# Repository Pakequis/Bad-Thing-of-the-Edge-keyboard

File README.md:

# **Bad Thing of the Edge keyboard**
A mechanical gamer keyboard for left hand with Raspberry Pi Pico.

## Why another mechanical keyboard?

Sometimes I play **Diablo 3** on my small 7-inch laptop and have difficulty with the keyboard. The keys are very small and the placement is a little different from a regular keyboard. Yes, I could remap the keys or use a regular keyboard, but it wouldn't be as fun as making my own keyboard.

The keyboard layout was made for my left hand with the main four fingers on the skills buttons and the thumb on the potion button.

~~It should work for Diablo 4 (the action keys are mostly in the same positions), but I haven't tested it yet (**$$$**). For other games, you need to change the buttons table in the firmware.~~

[Update 05/19/2024] I remapped the keys to work in both Diablo 3 and Diablo 4.

## Demo video:

## Hardware:

The boards were developed in kicad 7.0. There are two PCBs, one for the keyboard (Main-board) and another for the panel. The two boards are stacked and secured with M3 screws and 8 mm spacers.

External libraries used in the project:

[Key Switchs library for Kicad by Rafael Silva.](https://github.com/kiswitch/kiswitch)

[Raspberry Pi Pico by Nicolò Carandini.](https://github.com/ncarandini/KiCad-RP-Pico)

I used two-piece clear keycaps for the keys ([bought on Aliexpress](https://s.click.aliexpress.com/e/_DEuJarX) - **Affiliate link!**). I printed the button images, cut them out and put them inside the keycaps.

Bars for the LEDs were made into the panel board with keep out areas on the top and bottom copper layers and the bottom solder mask layer. When the LEDs on the main board turn on, the light is scattered on these bars. I used red LEDs to contrast with the black solder mask and match the horror theme of the keyboard.

The stack:

Mechanical keys are Cherry MX type, but in the prototype I took the keys from a old PTZ camera controller.

Files here are from the second version of the boards, with corrections made to the prototype. The photos and videos are from the prototype. One problem I had with the prototype panel board was that I didn't put the keep out area on the bottom solder mask layer. So I had to sand these areas and the effect was even better than I expected. Here the affected area:

Second board revision sponsored by [PCBWay](https://www.pcbway.com).

## Firmware:

The firmware was made in [VSCode](https://code.visualstudio.com/) with the [PlatformIO](https://platformio.org/) extension and the [Arduino-Pico core](https://github.com/earlephilhower/arduino-pico), using [Adafruit's TinyUSB library](https://github.com/adafruit/Adafruit_TinyUSB_Arduino). Core 0 is responsible for the keyboard and Core 1 for the LED effects. It was a bit over the top, but I wanted to test this functionality.

The keyboard part was made using the [example from Adafruit's TinyUSB library](https://github.com/adafruit/Adafruit_TinyUSB_Arduino/blob/master/examples/HID/hid_boot_keyboard/hid_boot_keyboard.ino).

The LED effects in this first version are:
- **Breath** - Up and down the bright of the LED bars.
- **Noise** - Random change in the bright of the bars.
- **Breath 2** - Same as the first one, but the center bar changes the brightness first.
- **Keypress** - Flashes the bars when a key is pressed.
- **Quake Flicker** - The classical [fluorescent Quake's flashing lights](https://github.com/Pakequis/arduino-quake-flicker-lamp).

One of the keys - the first one on the top - was exclusive to change the effect of the LEDs. When it is pressed, the bars flash indicating the change and the new effect starts working. Effects are saved in one byte of the FLASH memory and retrieved on power on.

## Bad Thing of What?
The name comes from a famous Brazilian case of haunted house and exorcism that happened in 1953. On one of the exorcism nights, Father Pedro Cintra asked in Latin: **"Praecipio ibi ut dicas qui sis tu"** ("I command you to tell me who you are"). A monstrous voice then replied in Portuguese: **"Eu sou o Diabo!"** ("I am the Devil!").

But people didn't pronounce that name and called the entity just **"Coisa Ruim"** ("Bad Thing", but "Evil Thing" would be better ) when the rumors spread. They added part of the name of the city where the case took place, **Borda da Mata** (something like "Edge of the Woods"), and started to call it Coisa Ruim da Borda (Bad Thing of the Edge).

I found an [article in a magazine of the time with a picture of the haunted house](http://memoria.bn.br/DocReader/DocReader.aspx?bib=003581&pagfis=86382) (in Portuguese - page 102).

## Known issues:
- The position of the Raspberry pi pico on the board is not good and some USB cables may not fit between the boards.
- It lacks a case for 3D printing. 
- The positioning of the LEDs could be improved.

## Contact:

Feel free to reach out to me on social media: @pakequis in any of them...

You can also send me an email at pakequis (Gmail).

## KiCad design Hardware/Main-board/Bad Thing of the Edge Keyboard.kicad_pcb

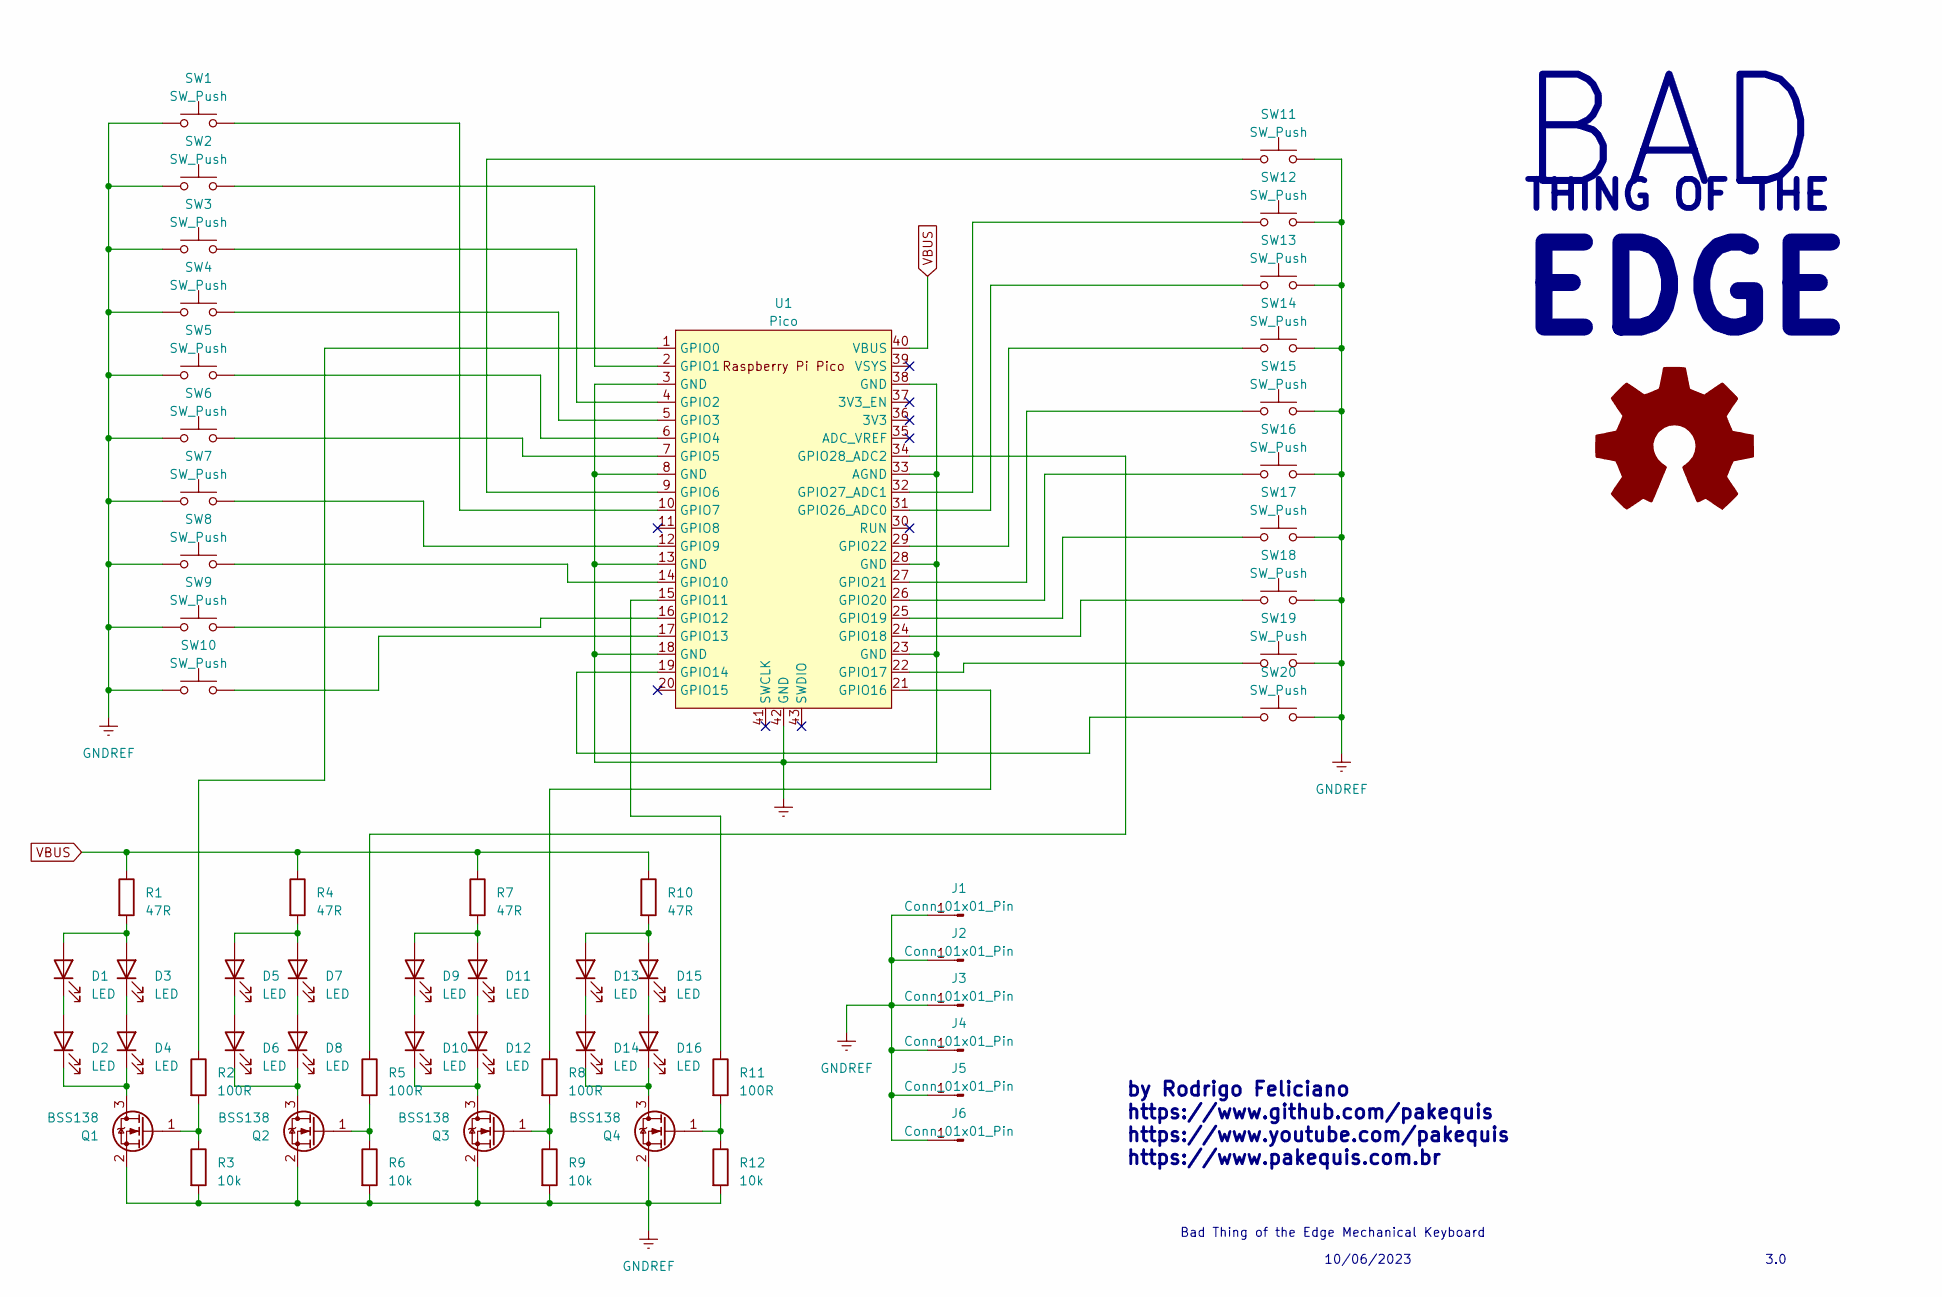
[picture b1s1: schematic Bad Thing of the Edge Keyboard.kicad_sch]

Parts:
D1, D2, D3, D4, D5, D6, D7, D8, D9, D10, D11, D12, D13, D14, D15, D16: LED; LED_0805_2012Metric_Pad1.15x1.40mm_HandSolder
J1, J2, J3, J4, J5, J6: Conn_01x01_Pin; MountingHole_3.2mm_M3_Pad
Q1, Q2, Q3, Q4: BSS138; SOT-23
R1, R4, R7, R10: 47R; R_0805_2012Metric_Pad1.20x1.40mm_HandSolder
R2, R5, R8, R11: 100R; R_0805_2012Metric_Pad1.20x1.40mm_HandSolder
R3, R6, R9, R12: 10k; R_0805_2012Metric_Pad1.20x1.40mm_HandSolder
SW1, SW2, SW3, SW4, SW5, SW6, SW7, SW8, SW9, SW10, SW11, SW12, SW13, SW14, SW15, SW16, SW17, SW18, SW19, SW20: SW_Push; SW_Cherry_MX_1.00u_PCB
U1: Pico; RPi_Pico_SMD_TH

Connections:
GNDREF: J1.1, J2.1, J3.1, J4.1, J5.1, J6.1, Q1.2 (S), Q2.2 (S), Q3.2 (S), Q4.2 (S), R3.2, R6.2, R9.2, R12.2, SW1.1, SW2.1, SW3.1, SW4.1, SW5.1, SW6.1, SW7.1, SW8.1, SW9.1, SW10.1, SW11.2, SW12.2, SW13.2, SW14.2, SW15.2, SW16.2, SW17.2, SW18.2, SW19.2, SW20.2, U1.3 (GND), U1.8 (GND), U1.13 (GND), U1.18 (GND), U1.23 (GND), U1.28 (GND), U1.33 (AGND), U1.38 (GND), U1.42 (GND)
unnamed: D1.2 (A), D3.2 (A), R1.2
unnamed: D1.1 (K), D2.2 (A)
unnamed: D2.1 (K), D4.1 (K), Q1.3 (D)
unnamed: D3.1 (K), D4.2 (A)
unnamed: D5.2 (A), D7.2 (A), R4.2
unnamed: D5.1 (K), D6.2 (A)
unnamed: D6.1 (K), D8.1 (K), Q2.3 (D)
unnamed: D7.1 (K), D8.2 (A)
unnamed: D9.1 (K), D10.2 (A)
unnamed: D10.1 (K), D12.1 (K), Q3.3 (D)
unnamed: D9.2 (A), D11.2 (A), R7.2
unnamed: D11.1 (K), D12.2 (A)
unnamed: D13.2 (A), D15.2 (A), R10.2
unnamed: D13.1 (K), D14.2 (A)
unnamed: D14.1 (K), D16.1 (K), Q4.3 (D)
unnamed: D15.1 (K), D16.2 (A)
unnamed: Q1.1 (G), R2.2, R3.1
unnamed: Q2.1 (G), R5.2, R6.1
unnamed: Q3.1 (G), R8.2, R9.1
unnamed: Q4.1 (G), R11.2, R12.1
unnamed: R2.1, U1.1 (GPIO0)
unnamed: SW2.2, U1.2 (GPIO1)
unnamed: SW3.2, U1.4 (GPIO2)
unnamed: SW4.2, U1.5 (GPIO3)
unnamed: SW5.2, U1.6 (GPIO4)
unnamed: SW6.2, U1.7 (GPIO5)
unnamed: SW11.1, U1.9 (GPIO6)
unnamed: SW1.2, U1.10 (GPIO7)
unnamed: SW7.2, U1.12 (GPIO9)
unnamed: SW8.2, U1.14 (GPIO10)
unnamed: R11.1, U1.15 (GPIO11)
unnamed: SW9.2, U1.16 (GPIO12)
unnamed: SW10.2, U1.17 (GPIO13)
unnamed: SW20.1, U1.19 (GPIO14)
unnamed: R8.1, U1.21 (GPIO16)
unnamed: SW19.1, U1.22 (GPIO17)
unnamed: SW18.1, U1.24 (GPIO18)
unnamed: SW17.1, U1.25 (GPIO19)
unnamed: SW16.1, U1.26 (GPIO20)
unnamed: SW15.1, U1.27 (GPIO21)
unnamed: SW14.1, U1.29 (GPIO22)
unnamed: SW13.1, U1.31 (GPIO26_ADC0)
unnamed: SW12.1, U1.32 (GPIO27_ADC1)
unnamed: R5.1, U1.34 (GPIO28_ADC2)
VBUS: R1.1, R4.1, R7.1, R10.1, U1.40 (VBUS)

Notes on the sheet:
by Rodrigo Feliciano https://www.github.com/pakequis https://www.youtube.com/pakequis https://www.pakequis.com.br
Bad Thing of the Edge Mechanical Keyboard
THING OF THE
BAD
3.0
EDGE
10/06/2023

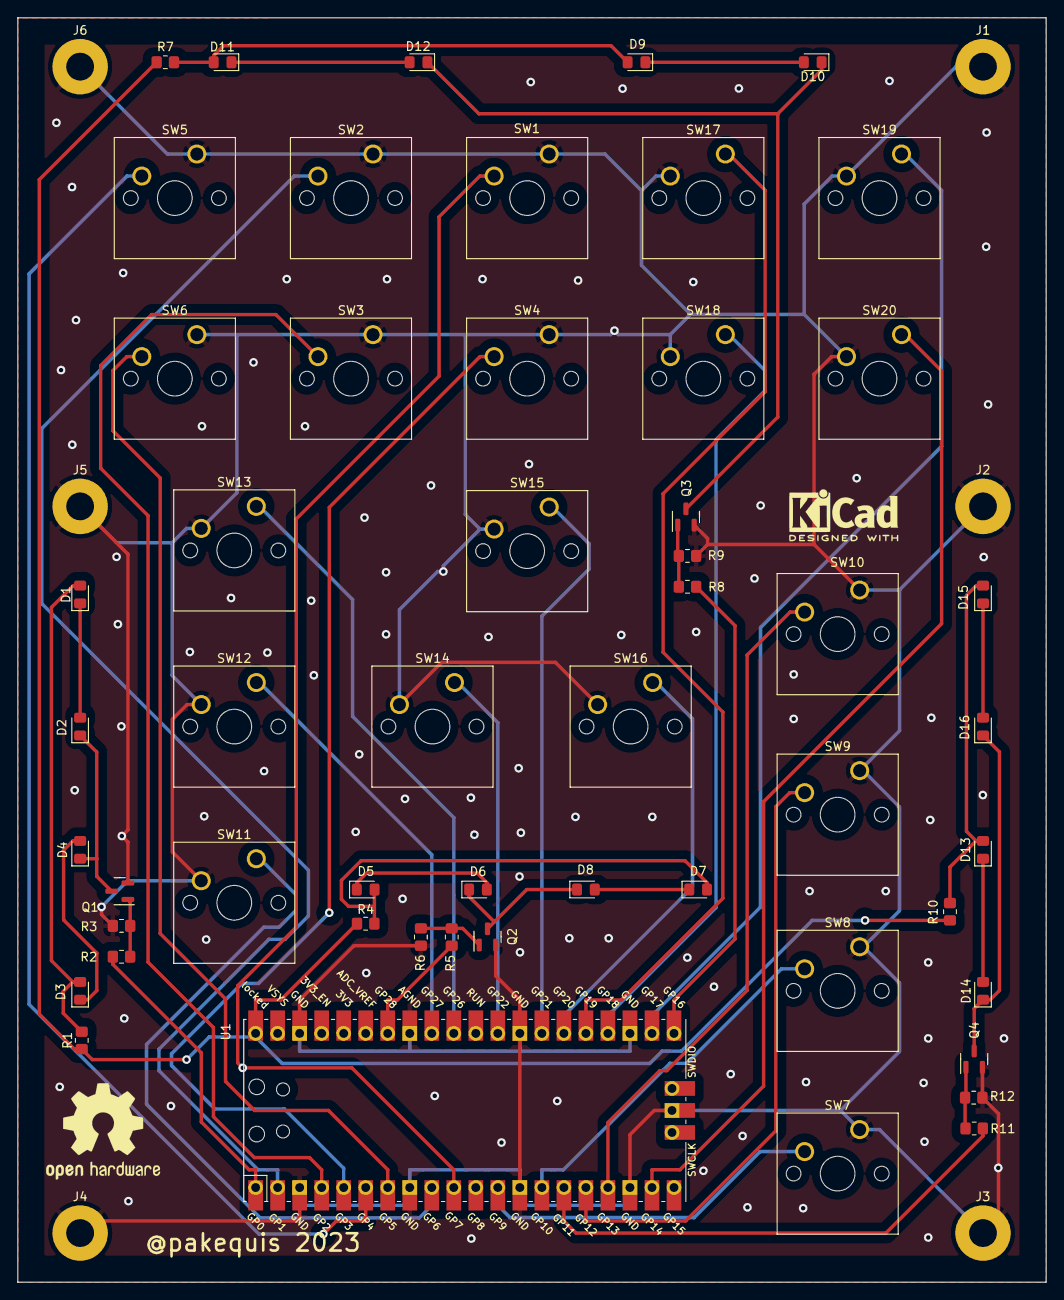
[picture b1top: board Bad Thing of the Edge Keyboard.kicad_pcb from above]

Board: 2 copper layers, 118.6 x 145.8 mm, 61 parts (0 on the bottom side), 46 nets.

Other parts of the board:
m1: OSHW-Logo2_14.6x12mm_SilkScreen
m2: KiCad-Logo2_5mm_SilkScreen

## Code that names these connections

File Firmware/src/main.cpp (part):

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    [h]          [i]
                 [j]

  0 SW5   GPIO4   | a SW13  GPIO26
  1 SW2   GPIO1   | b SW15  GPIO21
  2 SW1   GPIO7   | c SW10  GPIO13
  3 SW17  GPIO19  | d SW12  GPIO27
  4 SW19  GPIO17  | e SW14  GPIO22
  5 SW6   GPIO5   | f SW16  GPIO20
  6 SW3   GPIO2   | g SW9   GPIO12
  7 SW4   GPIO3   | h SW11  GPIO6
  8 SW18  GPIO18  | i SW8   GPIO10
  9 SW20  GPIO14  | j SW7   GPIO9
*/

/* Key pins */
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
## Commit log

2023-06-11 Create LICENSE
2023-07-18 Remap some keys for Diablo 3
2023-07-30 Main board revision 3
2024-04-20 Readme update
2024-05-19 Remapped the keys to work in Diablo 3 ando Diablo 4
2024-06-06 backups files removed
2024-12-28 add schematic
2025-01-19 OSHW certification mark
2026-04-08 Panel Typo
